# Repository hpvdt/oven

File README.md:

# Oven Control System

Our team's generic composite oven controller. Used to maintain a desired two-step curing 
cycle recommended for the majority of our composites. Each step is defined with a target 
temperature, a ramp speed to reach it at (e.g. 2 degC/minute), and hold time at that 
temperature.

The control system is pretty simple, a single K-type thermocouple is used to monitor the 
temperature in the oven, and a simple "ON/OFF" scheme is used to operate the relay that 
controls the power to the heater. Turning ON when below a threshold, and then OFF once 
the upper threshold is surpassed.

User input is handled by a 16 button keypad, with a 20 by 4 character LCD screen used for 
feedback to the user to inform them of their input, and the current state of the oven.

## Code

With the exception of the display code (under "libraries") all the code was written by hand 
in the Arduino IDE. The main firmware is `oven_system` which is written for an Arduino Nano.

It was previously modified to include logging capabilities (`oven_system_with_logging`), 
and another version to operate using the serial interface for input/output in the absence 
of a keybad and/or a screen (`oven_system_no_display`). ***These variants have not been 
maintained to include recent improvements to the main code!***

In addition to the main code, we also prepared unit tests for each piece of hardware we were 
introducing to the system. In these we wrote the code needed to interact with each part as 
well as running some basic tests to exercise both the code and component. These are all in 
the "unit_tests" folder.

## Hardware

The current design is a small circuit board which has the ATmega328P microcontroller and 
the MAX6675 thermocouple chip. The microcontroller is set up to be programmed just like 
an Arduino Nano. Off board is the solid state relay used to regulate the heater, the 5V 
supply, keypad, and screen. This is all housed in a metal case repurposed from a failed 
power supply, with the terminal block used to connect the thermocouple, power, and heater.

The current board was designed in KiCad 6, however my previous versions were designed in 
EAGLE. The most notable differences through iterations are:

- Embedding of the microcontroller and the MAX6675 directly to the main board
- Removal of the logging functionality since it was not used
- The earliest versions were designed to use thermistors instead of a thermocouple
- Previous designs weren't designed to fit in any particular enclosure

## TODO

A small to-do list of future features that could improve the system.

- [ ] Add some system to allow for recovery if power is interrupted
- [ ] Add some system to allow the system to be reset if needed
- [x] Figure out why SPI programming doesn't work if the MAX6675 is connected in any way
    - This was due to the MAX6675 not having a pullup on nCS, so it was active during programming of the ATmega and interfered on the SPI bus.
    - This **should** be revised in future hardware revisions

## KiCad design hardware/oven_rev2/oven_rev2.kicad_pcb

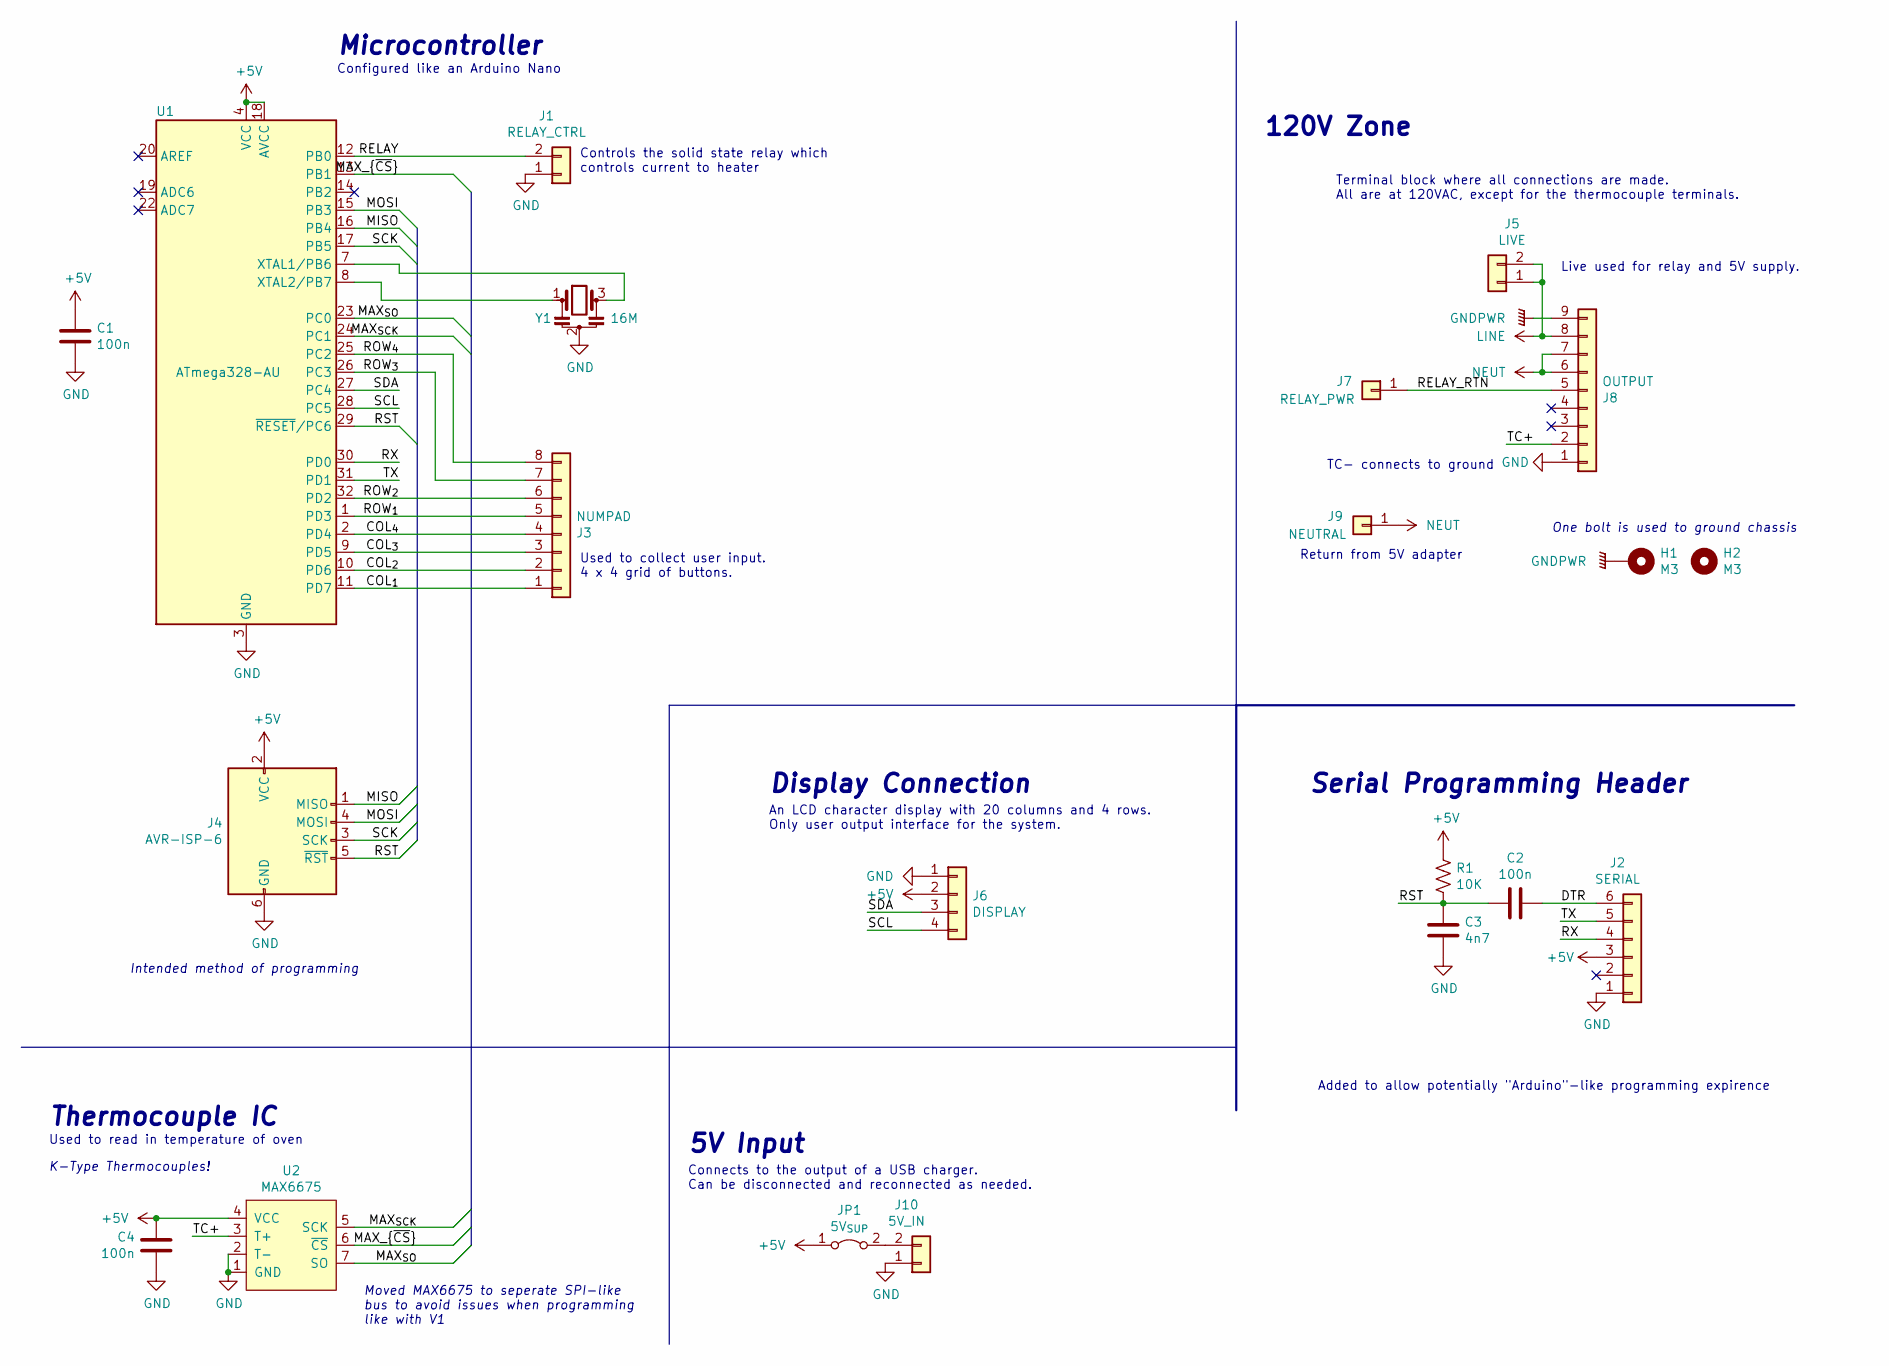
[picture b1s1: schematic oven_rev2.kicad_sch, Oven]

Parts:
C1, C2, C4: 100n; C_0603_1608Metric
C3: 4n7; C_0603_1608Metric
H1: M3; MountingHole_3.5mm_Pad_Via
H2: M3; MountingHole_3.5mm
J1: RELAY_CTRL; PinHeader_1x02_P2.54mm_Horizontal
J2: SERIAL; PinHeader_1x06_P2.54mm_Vertical
J3: NUMPAD; PinHeader_1x08_P2.54mm_Horizontal
J4: AVR-ISP-6; IDC-Header_2x03_P2.54mm_Vertical
J5: LIVE; SolderWire-2sqmm_1x02_P7.8mm_D2mm_OD3.9mm
J6: DISPLAY; PinHeader_1x04_P2.54mm_Horizontal
J7: RELAY_PWR; SolderWire-2sqmm_1x01_D2mm_OD3.9mm
J8: OUTPUT; 9POS-TERMBLOCK
J9: NEUTRAL; SolderWire-2sqmm_1x01_D2mm_OD3.9mm
J10: 5V_IN; PinHeader_1x02_P2.54mm_Horizontal
JP1: 5V_{SUP}; SolderJumper-2_P1.3mm_Bridged_Pad1.0x1.5mm
R1: 10K; R_0603_1608Metric
U1: ATmega328-AU; TQFP-32_7x7mm_P0.8mm
U2: MAX6675; SO-8_5.3x6.2mm_P1.27mm
Y1: 16M; Resonator_SMD_muRata_CSTxExxV-3Pin_3.0x1.1mm

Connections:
+5V: C1.2, C4.2, J2.3, J4.2 (VCC), J6.2, JP1.1 (A), R1.1, U1.4 (VCC), U1.6 (VCC), U1.18 (AVCC), U2.4 (VCC)
/COL_{1}: J3.1, U1.11 (PD7)
/COL_{2}: J3.2, U1.10 (PD6)
/COL_{3}: J3.3, U1.9 (PD5)
/COL_{4}: J3.4, U1.2 (PD4)
/DTR: C2.1, J2.6
/MAX_{SCK}: U1.24 (PC1), U2.5 (SCK)
/MAX_{SO}: U1.23 (PC0), U2.7 (SO)
/MAX_{~CS}: U1.13 (PB1), U2.6 (~CS)
/MISO: J4.1 (MISO), U1.16 (PB4)
/MOSI: J4.4 (MOSI), U1.15 (PB3)
/RELAY: J1.2, U1.12 (PB0)
/RELAY_RTN: J7.1, J8.5
/ROW_{1}: J3.5, U1.1 (PD3)
/ROW_{2}: J3.6, U1.32 (PD2)
/ROW_{3}: J3.7, U1.26 (PC3)
/ROW_{4}: J3.8, U1.25 (PC2)
/RST: C2.2, C3.2, J4.5 (~RST), R1.2, U1.29 (~RESET/PC6)
/RX: J2.4, U1.30 (PD0)
/SCK: J4.3 (SCK), U1.17 (PB5)
/SCL: J6.4, U1.28 (PC5)
/SDA: J6.3, U1.27 (PC4)
/TC+: J8.2, U2.3 (T+)
/TX: J2.5, U1.31 (PD1)
GND: C1.1, C3.1, C4.1, J1.1, J2.1, J4.6 (GND), J6.1, J8.1, J10.1, U1.3 (GND), U1.5 (GND), U1.21 (GND), U2.1 (GND), U2.2 (T-), Y1.2
GNDPWR: H1.1, J8.9
LINE: J5.1, J5.2, J8.8
NEUT: J8.6, J8.7, J9.1
unnamed: J10.2, JP1.2 (B)
unnamed: U1.7 (XTAL1/PB6), Y1.3
unnamed: U1.8 (XTAL2/PB7), Y1.1

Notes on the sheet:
Moved MAX6675 to seperate SPI-like bus to avoid issues when programming like with V1
One bolt is used to ground chassis
Live used for relay and 5V supply.
Used to read in temperature of oven
120V Zone
Controls the solid state relay which controls current to heater
Microcontroller
5V Input
Display Connection
Return from 5V adapter
Connects to the output of a USB charger. Can be disconnected and reconnected as needed.
Intended method of programming
An LCD character display with 20 columns and 4 rows. Only user output interface for the system.
Added to allow potentially "Arduino"-like programming expirence
TC- connects to ground
Configured like an Arduino Nano
Serial Programming Header
Thermocouple IC
K-Type Thermocouples!
Terminal block where all connections are made. All are at 120VAC, except for the thermocouple terminals.
Used to collect user input. 4 x 4 grid of buttons.

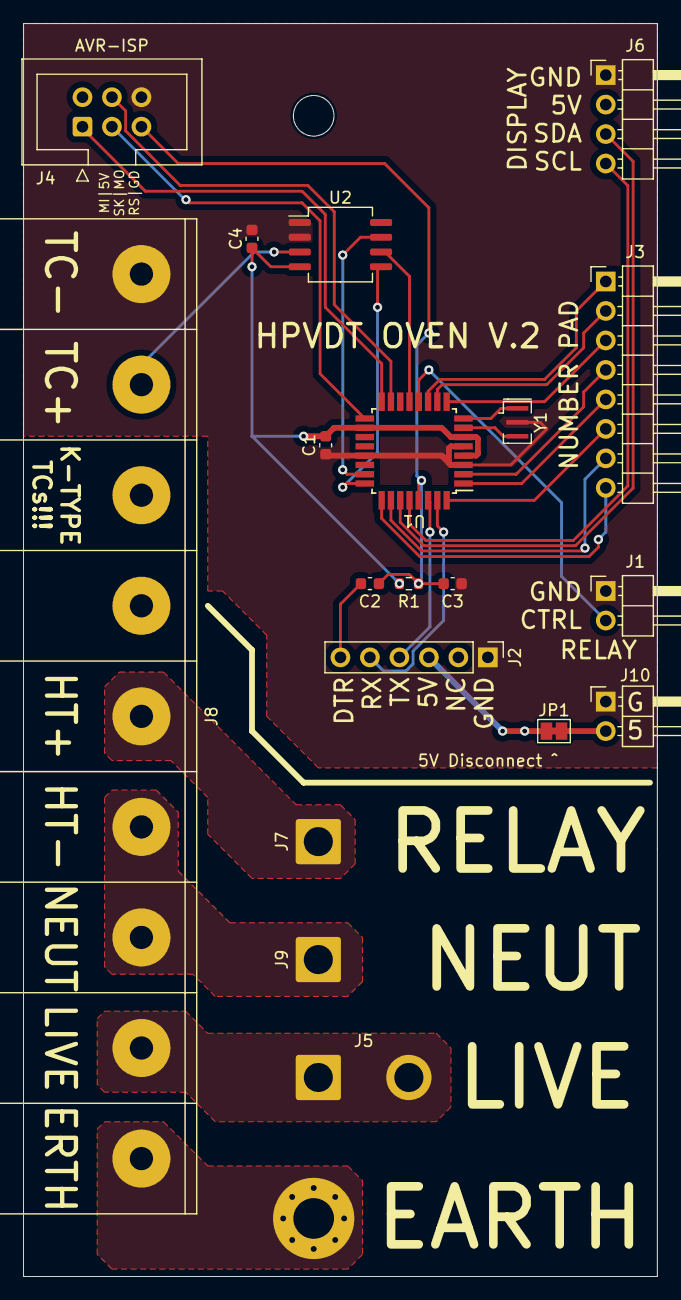
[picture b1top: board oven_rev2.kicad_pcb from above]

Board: 2 copper layers, 54.6 x 108.0 mm, 21 parts (0 on the bottom side), 31 nets.

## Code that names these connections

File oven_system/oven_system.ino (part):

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// Keypad works by detecting the intersection of a row and col pulling down an input. (A column pulling the row down)

// MAX6675 Pins
const byte MAX_SCK = A1;
const byte MAX_CS = 9;
const byte MAX_SO = A0;

// Heater 
const byte heater = 12;  // Heater relay pin
bool heaterState;       // State variable

// Control variables
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  pinMode(row1, INPUT_PULLUP); pinMode(row2, INPUT_PULLUP); pinMode(row3, INPUT_PULLUP); pinMode(row4, INPUT_PULLUP);
  pinMode(col1, OUTPUT); pinMode(col2, OUTPUT); pinMode(col3, OUTPUT); pinMode(col4, OUTPUT);

  pinMode(heater, OUTPUT);            // Controls relay
  heaterState = LOW;                  // Off by default
  digitalWrite(heater, heaterState);

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
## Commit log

2021-06-07 Upload of hardware files
2021-06-07 Upload of unit tests for parts
2021-06-07 Initial upload of oven system code
2021-06-07 Moved to unit test folder
2021-06-07 Moved ionto unit test folder
2021-06-07 Rename unit_tests/display_test.ino to unit_tests/display_test/display_test.ino
2021-06-07 Moved into unit test folder
2021-06-07 Rename LCD.h to libraries/Newliquidcrystal_1.3.5/LCD.h
2021-06-07 Partial upload of LCD library
2021-06-11 Breaking main file down into seperate files
2021-06-11 Added code to operate using MAX6675
2021-06-15 Accounting for millis() inaccuracy
2022-03-16 Added MAX6675 unit test code
2022-03-16 Reworking hardware folder
2022-03-16 Uploaded reorganized hardware folder
2022-03-16 Accomodate new board design in code
2022-03-16 Added media for readme
2022-03-16 Added images to readme
2022-03-25 Updated oven revision to have buzzer
2023-12-08 Moved code into firmware folder
2023-12-08 Update README.md
    Added cause and remedy for programming issues related to MAX6675 chip
2024-02-14 Changed hardware organisation, updated to KiCad 7
2024-02-14 Started rev 3 project
2024-02-14 Removed unrelated gerbers from rev 3
2024-02-14 Moved Arduino code into a directory
2024-02-14 Removed unneed hardware files
2024-02-14 Updated `.gitignore`s
2024-02-14 Added KiCad `.gitignore`
2024-02-14 Created PlatformIO project for oven
2024-02-14 Tidied up keypad code
    Changed indenting to 4 spaces, made short delays use `delayMicroseconds`, added comments for functions.
2024-02-14 Generalized the temperature code
2024-02-14 Added support for switching between MAX chips
2024-02-14 Added `lcd` dependancy to header
2024-02-14 Fixed logic for second ramp
2024-02-14 Tidied up main code
    Lots of small changes:
    - Made lots of one line control statements single line
    - Changed `fields` to be a two dimensional array for easier reading
    - Changed code to avoid over shooting rather than undershooting (with configurable tolerance)
2024-02-14 Touched up title blocks and rev 3
2024-02-14 Minor touchups for titleblocks
2024-02-14 Removed buzzer that was not present in fabricated boards
2024-02-14 Fixed pin allocations for rev 2 board
2024-02-14 Minor touchups for temperature reading
2024-02-14 Proper masking of MAX6675 status bit
2024-02-14 Reduced scope of some variables
2024-02-14 Added trim for measured inaccuracy of resonator
2024-02-23 Added ability to exit baking
2024-04-05 Added watchdog reset
2024-05-11 Extended watchdog timer to allow reset to be keyed
2024-05-11 Can skip second stage
    Added ability to skip second stage is only a single stage cure is desired by having the second stage temperature lower than the first
